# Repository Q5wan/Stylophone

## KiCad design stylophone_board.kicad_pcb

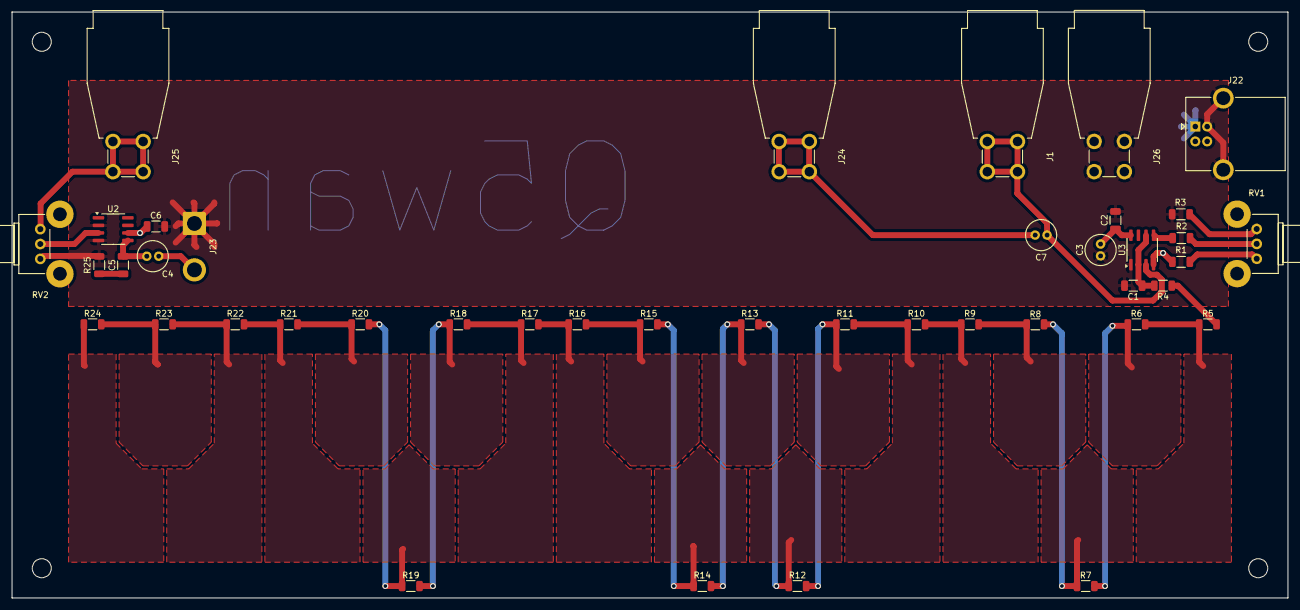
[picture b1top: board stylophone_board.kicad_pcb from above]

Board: 2 copper layers, 214.5 x 98.5 mm, 46 parts (0 on the bottom side), 34 nets.

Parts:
C1: 33nF; C_1206_3216Metric
C2, C6: 100nF; C_1206_3216Metric
C3, C4, C7: 100uF; C_Radial_D5.0mm_H11.0mm_P2.00mm
C5: 50nF; C_1206_3216Metric
J1: Stylus; CalTest_CT3151
J22: USB_B; USB_B_OST_USB-B1HSxx_Horizontal
J23: Conn_01x02_Pin; SolderWire-2sqmm_1x02_P7.8mm_D2mm_OD3.9mm
J24: SIGNAL_OUT; CalTest_CT3151
J25: AMP; CalTest_CT3151
J26: GND; CalTest_CT3151
R1: 1k0; R_1206_3216Metric
R2: 4k7; R_1206_3216Metric
R3: 3k3; R_1206_3216Metric
R4: 61k9; R_1206_3216Metric
R5: 1k93; R_1206_3216Metric
R6: 3k79; R_1206_3216Metric
R7: 4k02; R_1206_3216Metric
R8: 4k27; R_1206_3216Metric
R9: 4k53; R_1206_3216Metric
R10: 4k75; R_1206_3216Metric
R11: 5k11; R_1206_3216Metric
R12: 5k36; R_1206_3216Metric
R13: 5k69; R_1206_3216Metric
R14: 6k04; R_1206_3216Metric
R15: 6k34; R_1206_3216Metric
R16: 6k73; R_1206_3216Metric
R17: 7k15; R_1206_3216Metric
R18: 7k59; R_1206_3216Metric
R19: 8k06; R_1206_3216Metric
R20: 8k56; R_1206_3216Metric
R21: 9k09; R_1206_3216Metric
R22: 9k53; R_1206_3216Metric
R23: 10k1; R_1206_3216Metric
R24: 10k7; R_1206_3216Metric
R25: 10R; R_1206_3216Metric
REF01, REF02, REF03, REF04: MountingHole_3.2mm_M3
RV1: 4k7; Potentiometer_Bourns_PTV09A-2_Single_Horizontal
RV2: 10k; Potentiometer_Bourns_PTV09A-2_Single_Horizontal
U2: LM386; SOIC-8_3.9x4.9mm_P1.27mm
U3: LM555xM; SOIC-8_3.9x4.9mm_P1.27mm

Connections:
GND: C1.2, C2.2, C3.2, C6.2, J22.4 (GND), J22.5 (Shield), J23.1, J26.1, R3.1, R25.1, RV2.3, U2.2 (-), U2.4 (GND), U3.1 (GND)
unnamed: C4.1, C5.2, U2.5
unnamed: C5.1, R25.2
unnamed: C7.1, J1.1, U3.3 (Q)
unnamed: R5.1, R6.2
unnamed: R6.1, R7.2
unnamed: R7.1, R8.2
unnamed: R8.1, R9.2
unnamed: R9.1, R10.2
unnamed: R10.1, R11.2
unnamed: R11.1, R12.2
unnamed: R12.1, R13.2
unnamed: R13.1, R14.2
unnamed: R14.1, R15.2
unnamed: R15.1, R16.2
unnamed: R16.1, R17.2
unnamed: R17.1, R18.2
unnamed: R18.1, R19.2
unnamed: R19.1, R20.2
unnamed: R20.1, R21.2
unnamed: R21.1, R22.2
unnamed: R22.1, R23.2
unnamed: R23.1, R24.2
unnamed: C4.2, J23.2
unnamed: C7.2, J24.1
unnamed: J25.1, RV2.1
unnamed: R1.2, RV1.1
unnamed: R2.1, RV1.2
unnamed: R3.2, RV1.3
unnamed: R4.1, R5.2
unnamed: RV2.2, U2.3 (+)
unnamed: R2.2, U3.5 (CV)
unnamed: C1.1, R4.2, U3.2 (TR), U3.6 (THR)
VCC: C2.1, C3.1, C6.1, J22.1 (VBUS), R1.1, U2.6 (V+), U3.4 (R), U3.8 (VCC)
